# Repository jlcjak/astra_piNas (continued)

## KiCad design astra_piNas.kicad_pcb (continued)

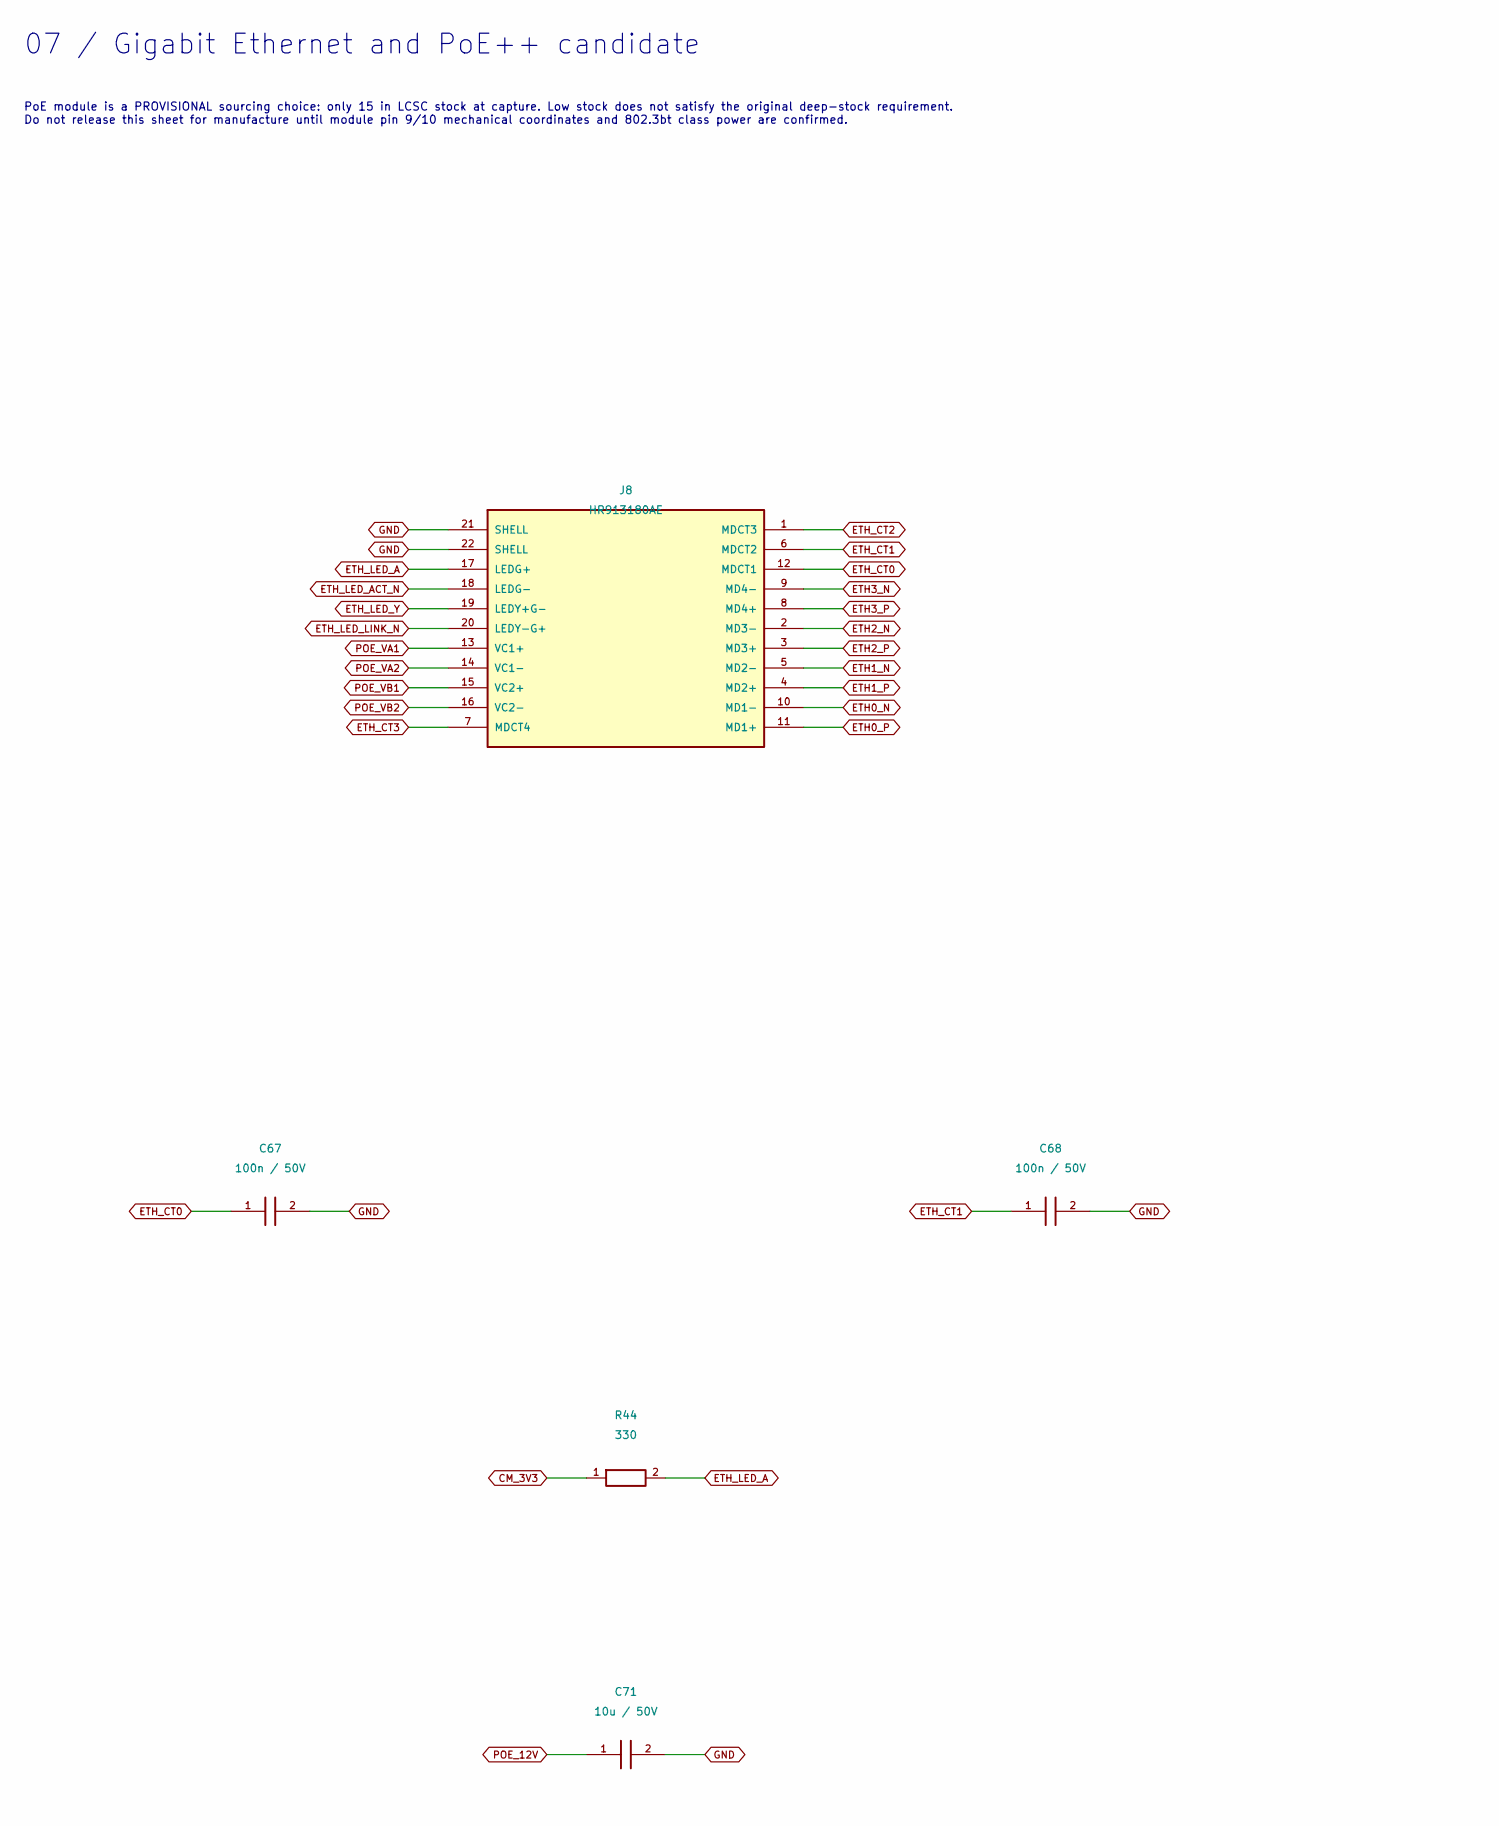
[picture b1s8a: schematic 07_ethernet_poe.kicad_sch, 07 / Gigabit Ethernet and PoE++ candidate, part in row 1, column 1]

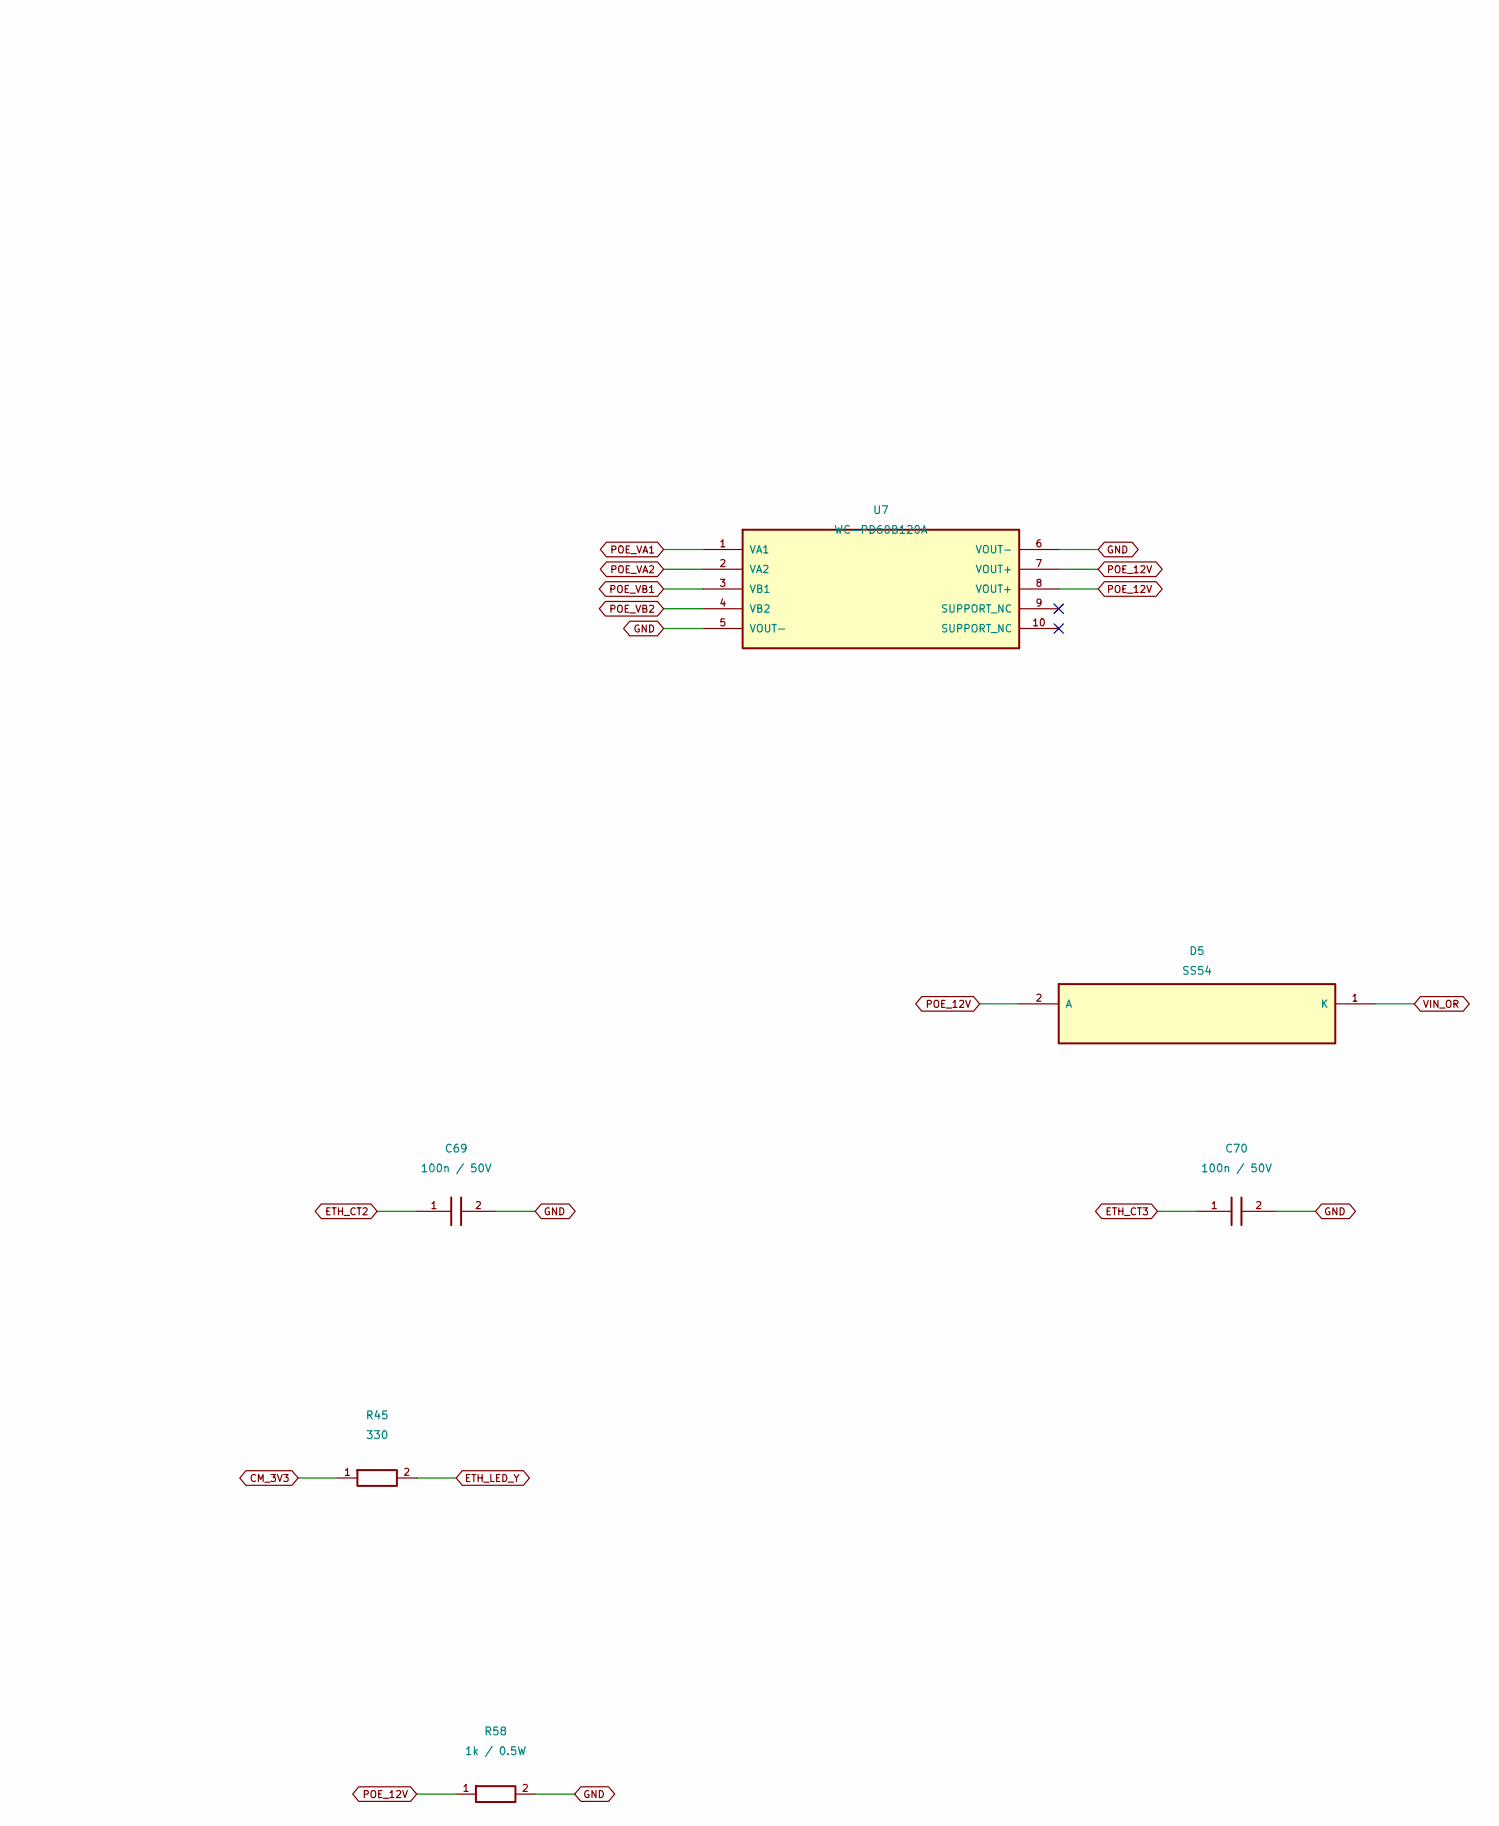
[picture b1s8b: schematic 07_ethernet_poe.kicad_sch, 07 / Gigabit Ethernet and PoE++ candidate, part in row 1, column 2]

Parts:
C67, C68, C69, C70: 100n / 50V; C_0603_1608Metric; MANUFACTURER PART NUMBER CL10B104KB8NNNC; LCSC Part Number C1591
C71: 10u / 50V; C_1206_3216Metric; MANUFACTURER PART NUMBER CL31B106KAHNNNE; LCSC Part Number C14860
D5: SS54; SMA_L4.4-W2.8-LS5.4-RD; MANUFACTURER PART NUMBER SS54; LCSC Part Number C123946
J8: HR913180AE; RJ45-TH_HR913180AE; MANUFACTURER PART NUMBER HR913180AE; LCSC Part Number C19724762
R44, R45: 330; R_0603_1608Metric; MANUFACTURER PART NUMBER 0603WAF3300T5E; LCSC Part Number C23138
R58: 1k / 0.5W; R_1206_3216Metric; MANUFACTURER PART NUMBER ESR18EZPF1001; LCSC Part Number C2074262
U7: WC-PD60B120A; WC_PD60B120A_MECHANICAL_REVIEW; MANUFACTURER PART NUMBER WC-PD60B120A; LCSC Part Number C2848082

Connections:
CM_3V3: R44.1, R45.1; also elsewhere on the board
ETH0_N: J8.10 (MD1-); also elsewhere on the board
ETH0_P: J8.11 (MD1+); also elsewhere on the board
ETH1_N: J8.5 (MD2-); also elsewhere on the board
ETH1_P: J8.4 (MD2+); also elsewhere on the board
ETH2_N: J8.2 (MD3-); also elsewhere on the board
ETH2_P: J8.3 (MD3+); also elsewhere on the board
ETH3_N: J8.9 (MD4-); also elsewhere on the board
ETH3_P: J8.8 (MD4+); also elsewhere on the board
ETH_CT0: C67.1, J8.12 (MDCT1)
ETH_CT1: C68.1, J8.6 (MDCT2)
ETH_CT2: C69.1, J8.1 (MDCT3)
ETH_CT3: C70.1, J8.7 (MDCT4)
ETH_LED_A: J8.17 (LEDG+), R44.2
ETH_LED_ACT_N: J8.18 (LEDG-); also elsewhere on the board
ETH_LED_LINK_N: J8.20 (LEDY-G+); also elsewhere on the board
ETH_LED_Y: J8.19 (LEDY+G-), R45.2
GND: C67.2, C68.2, C69.2, C70.2, C71.2, J8.21 (SHELL), J8.22 (SHELL), R58.2, U7.5 (VOUT-), U7.6 (VOUT-); also elsewhere on the board
POE_12V: C71.1, D5.2 (A), R58.1, U7.7 (VOUT+), U7.8 (VOUT+)
POE_VA1: J8.13 (VC1+), U7.1 (VA1)
POE_VA2: J8.14 (VC1-), U7.2 (VA2)
POE_VB1: J8.15 (VC2+), U7.3 (VB1)
POE_VB2: J8.16 (VC2-), U7.4 (VB2)
VIN_OR: D5.1 (K); also elsewhere on the board

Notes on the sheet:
07 / Gigabit Ethernet and PoE++ candidate
PoE module is a PROVISIONAL sourcing choice: only 15 in LCSC stock at capture. Low stock does not satisfy the original deep-stock requirement. Do not release this sheet for manufacture until module pin 9/10 mechanical coordinates and 802.3bt class power are confirmed.

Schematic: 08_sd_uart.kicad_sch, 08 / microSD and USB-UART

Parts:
C72, C74, C75, C76: 100n / 50V; C_0603_1608Metric; MANUFACTURER PART NUMBER CL10B104KB8NNNC; LCSC Part Number C1591
C73: 22u / 25V; C_0805_2012Metric; MANUFACTURER PART NUMBER CL21A226MAQNNNE; LCSC Part Number C45783
J7: TYPE-C-31-M-12; USB-C_SMD-TYPE-C-31-M-12_1; MANUFACTURER PART NUMBER TYPE-C-31-M-12; LCSC Part Number C165948
J9: TF-01A; TF-SMD_TF-01A; MANUFACTURER PART NUMBER TF-01A; LCSC Part Number C91145
R46, R47, R48, R49, R50: 10k; R_0603_1608Metric; MANUFACTURER PART NUMBER RC0603FR-0710KL; LCSC Part Number C98220
R51, R52: 5.1k; R_0603_1608Metric; MANUFACTURER PART NUMBER 0603WAF5101T5E; LCSC Part Number C23186
R53, R54: 330; R_0603_1608Metric; MANUFACTURER PART NUMBER 0603WAF3300T5E; LCSC Part Number C23138
U8: RT9742GGJ5; TSOT-23-5_L2.9-W1.6-P0.95-LS2.8-BR; MANUFACTURER PART NUMBER RT9742GGJ5; LCSC Part Number C250547
U9: CH343P; TQFN-16_L3.0-W3.0-P0.50-BL-EP1.7; MANUFACTURER PART NUMBER CH343P; LCSC Part Number C2846043
U10: USBLC6-2SC6; SOT-23-6_L2.9-W1.6-P0.95-LS2.8-BL; MANUFACTURER PART NUMBER USBLC6-2SC6; LCSC Part Number C7519

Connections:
CM_3V3: C72.1, C76.1, U8.5 (VIN), U9.1 (VIO); also elsewhere on the board
GND: C72.2, C73.2, C74.2, C75.2, C76.2, J7.1 (EH), J7.2 (EH), J7.3 (EH), J7.4 (EH), J7.A1B12 (GND), J7.B1A12 (GND), J9.6 (VSS), J9.10 (GND), J9.11 (GND), J9.12 (GND), J9.13 (GND), R51.2, R52.2, U8.2 (GND), U9.2 (GND), U9.17 (EP), U10.2; also elsewhere on the board
SD_3V3: C73.1, J9.4 (VDD), R46.1, R47.1, R48.1, R49.1, R50.1, U8.1 (VOUT)
SD_CLK: J9.5 (CLK(SCLK)); also elsewhere on the board
SD_CMD: J9.3 (CMD(DI)), R46.2; also elsewhere on the board
SD_DAT0: J9.7 (DAT0(D0)), R47.2; also elsewhere on the board
SD_DAT1: J9.8 (DAT1(RSV)), R48.2; also elsewhere on the board
SD_DAT2: J9.1 (DAT2(RSV)), R49.2; also elsewhere on the board
SD_DAT3: J9.2 (CDDAT3(CS)), R50.2; also elsewhere on the board
SD_PWR_EN: U8.4 (EN/~EN); also elsewhere on the board
UART_CC1: J7.A5 (CC1), R51.1
UART_CC2: J7.B5 (CC2), R52.1
UART_RX_BRIDGE: R54.2, U9.5 (RXD)
UART_RX_CM: R53.2; also elsewhere on the board
UART_TX_BRIDGE: R53.1, U9.4 (TXD)
UART_TX_CM: R54.1; also elsewhere on the board
UART_USB_N: J7.A7 (DN1), J7.B7 (DN2), U9.8 (UD-), U10.3, U10.4
UART_USB_P: J7.A6 (DP1), J7.B6 (DP2), U9.7 (UD+), U10.1, U10.6
UART_V3: C75.1, U9.6 (V3)
UART_VBUS: C74.1, J7.A4B9 (VBUS), J7.B4A9 (VBUS), U9.3 (VDD5), U9.9 (VBUS), U10.5

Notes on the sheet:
08 / microSD and USB-UART
USB-UART is independently powered by its USB cable; VIO follows CM5 3.3 V. No connection between debug VBUS and SYS_5V. GPIO14/15 UART requires OS configuration; this is not the separate CM5 on-module boot-debug UART.

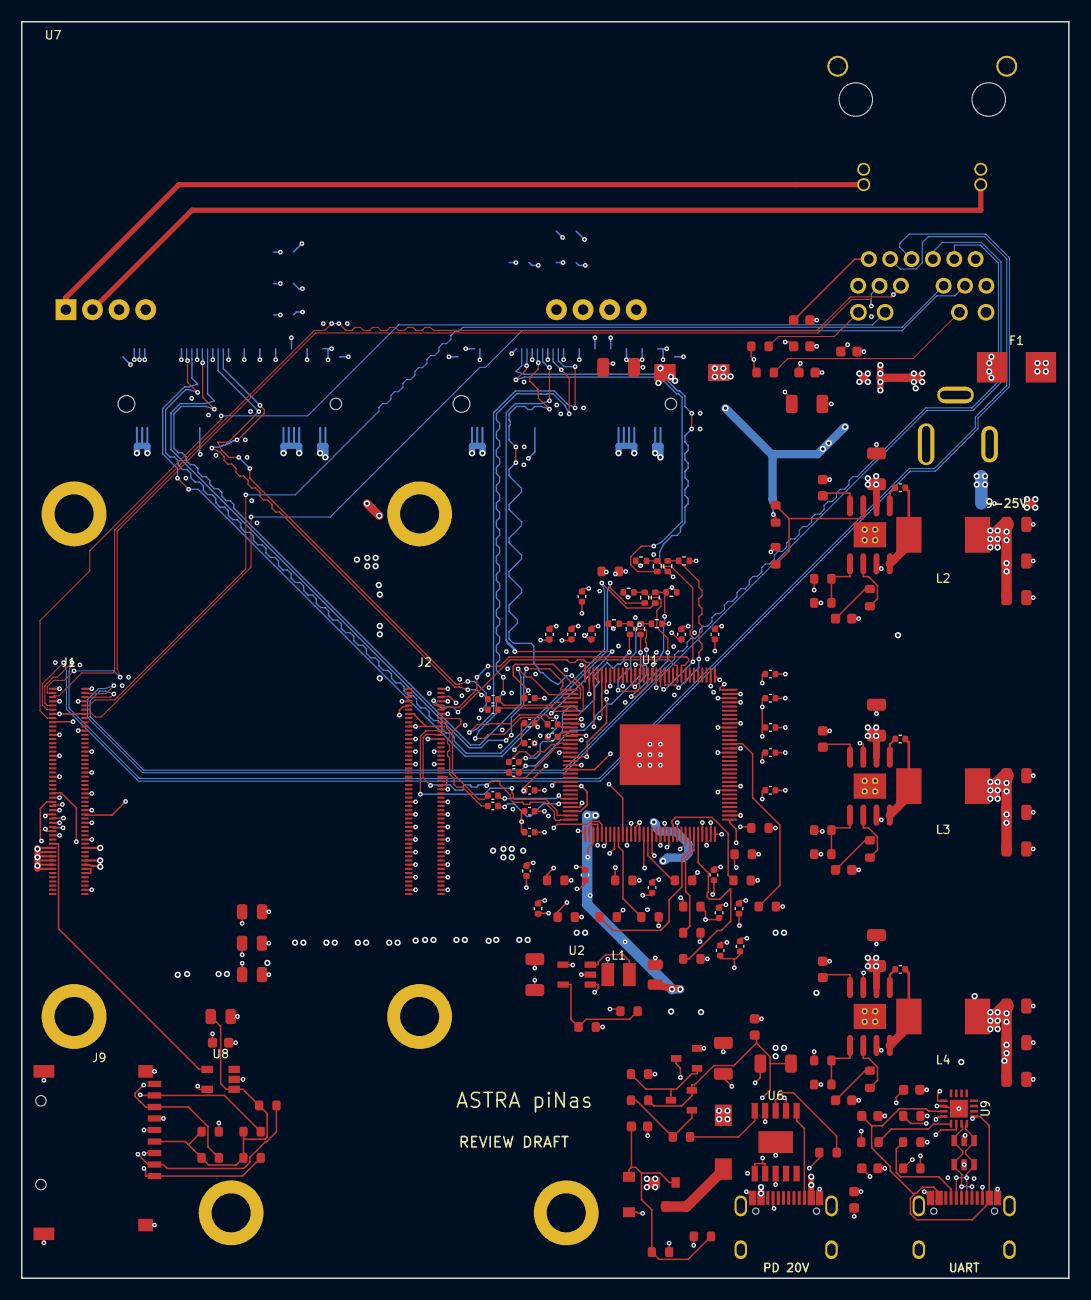
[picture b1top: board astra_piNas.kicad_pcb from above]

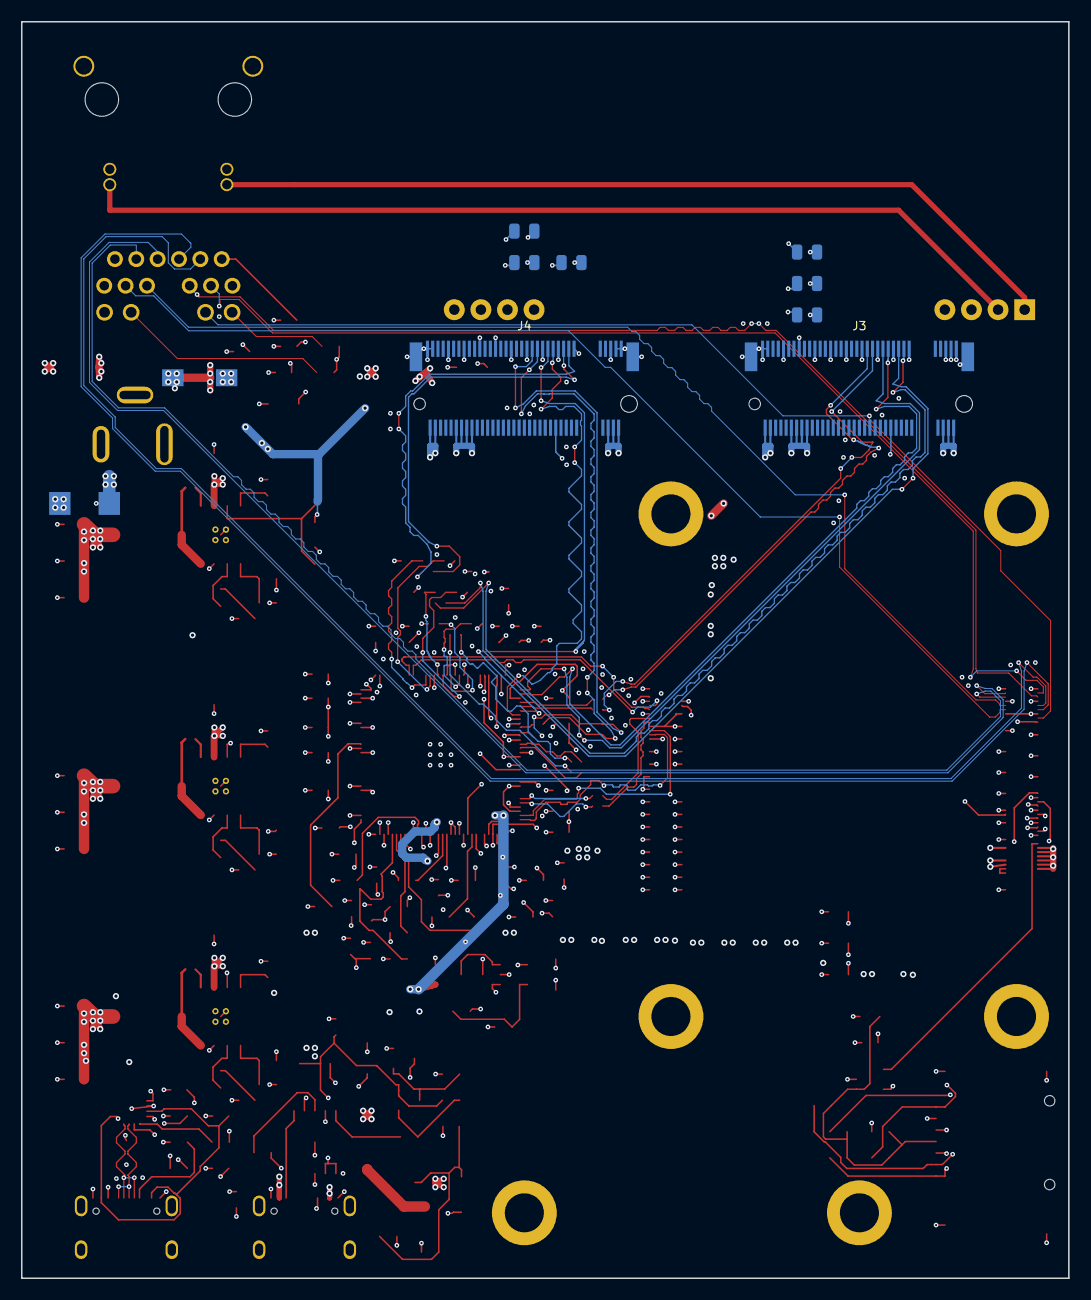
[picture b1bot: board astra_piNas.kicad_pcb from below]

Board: 6 copper layers, 100.0 x 120.0 mm, 176 parts (12 on the bottom side), 133 nets.
